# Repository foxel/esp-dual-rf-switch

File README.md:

# LightFox Dual - ESP8266 Dual RF switch for lights

## Connecting the board

The board has following connectors:
* mains connector with sqrew terminals (`Lin`, `L1`, `L2`, `N`). Mains supply should be connected to `Lin` and one of `N` terminals. The loads are connected to `L1`/`L2` and one of `N` terminals.
* ISP connector for ATTiny flashing. Pins are (from left to right): `RST`, `MOSI`, `MISO`, `SCL`)
* switches output connector for debug, etc. These are connected to ATTiny outputs controlling triacs. Pins are (from left to right): `L1`, `L2`, `3V3`, `GND`.

## Schematics

## Layout

## Firmware

There are two microcontrollers to run this switch
* **ESP-01** - use one of available firmware options:
  * ESPurna firmware: https://github.com/foxel/espurna/tree/lightfox-dual
  * Tasmota firmware: https://github.com/foxel/Sonoff-Tasmota/tree/foxel_dual_rf

* **ATTINY441** - firmware is in `attiny-firmware` folder. This requires [ATTinyCore](https://github.com/SpenceKonde/ATTinyCore) to build

To flash ESP module connect it to PC any available way (e.g. USB-Serail adapter + breadboard) and follow selected firmware option flashing instructions.

To flash ATTINY:
* remove ESP-01 module from the header
* connect ISP programmer (i.e. Arduino flashed with ArduinoISP) to ISP port
* use Arduino to flash MC: board is ATTiny441 (installed from [ATTinyCore](https://github.com/SpenceKonde/ATTinyCore))

## BOM

Item | Qty | Reference(s) | Link
-----|-----|--------------|------
100uF, 5v | 1 | C1 | 
3mm red LED | 2 | D1, D2 | 
BTA08-600BW | 2 | D3, D4 | 
1A fuse | 1 | F1 | 
Screw Terminal 01x03 | 2 | J1, J3 | 
4pin header | 2 | J2, J4 | 
470R, 0.125W | 2 | R1, R2 | 
150R, 0.125W | 2 | R3, R4 | 
390R, 0.5W | 2 | R5, R7 | 
470R, 0.5W | 2 | R6, R8 | 
10K, 0.125W | 1 | R9 | 
Itead.cc RF receiver | 1 | RF1 | https://www.itead.cc/rf-receiver-module-433mhz.html
ATTINY441-SSU | 1 | U1 | 
ESP-01S | 1 | U2 | 
MOC3043M/MOC3063M | 2 | U3, U4 | 
HLK-PM03 | 1 | U5 |

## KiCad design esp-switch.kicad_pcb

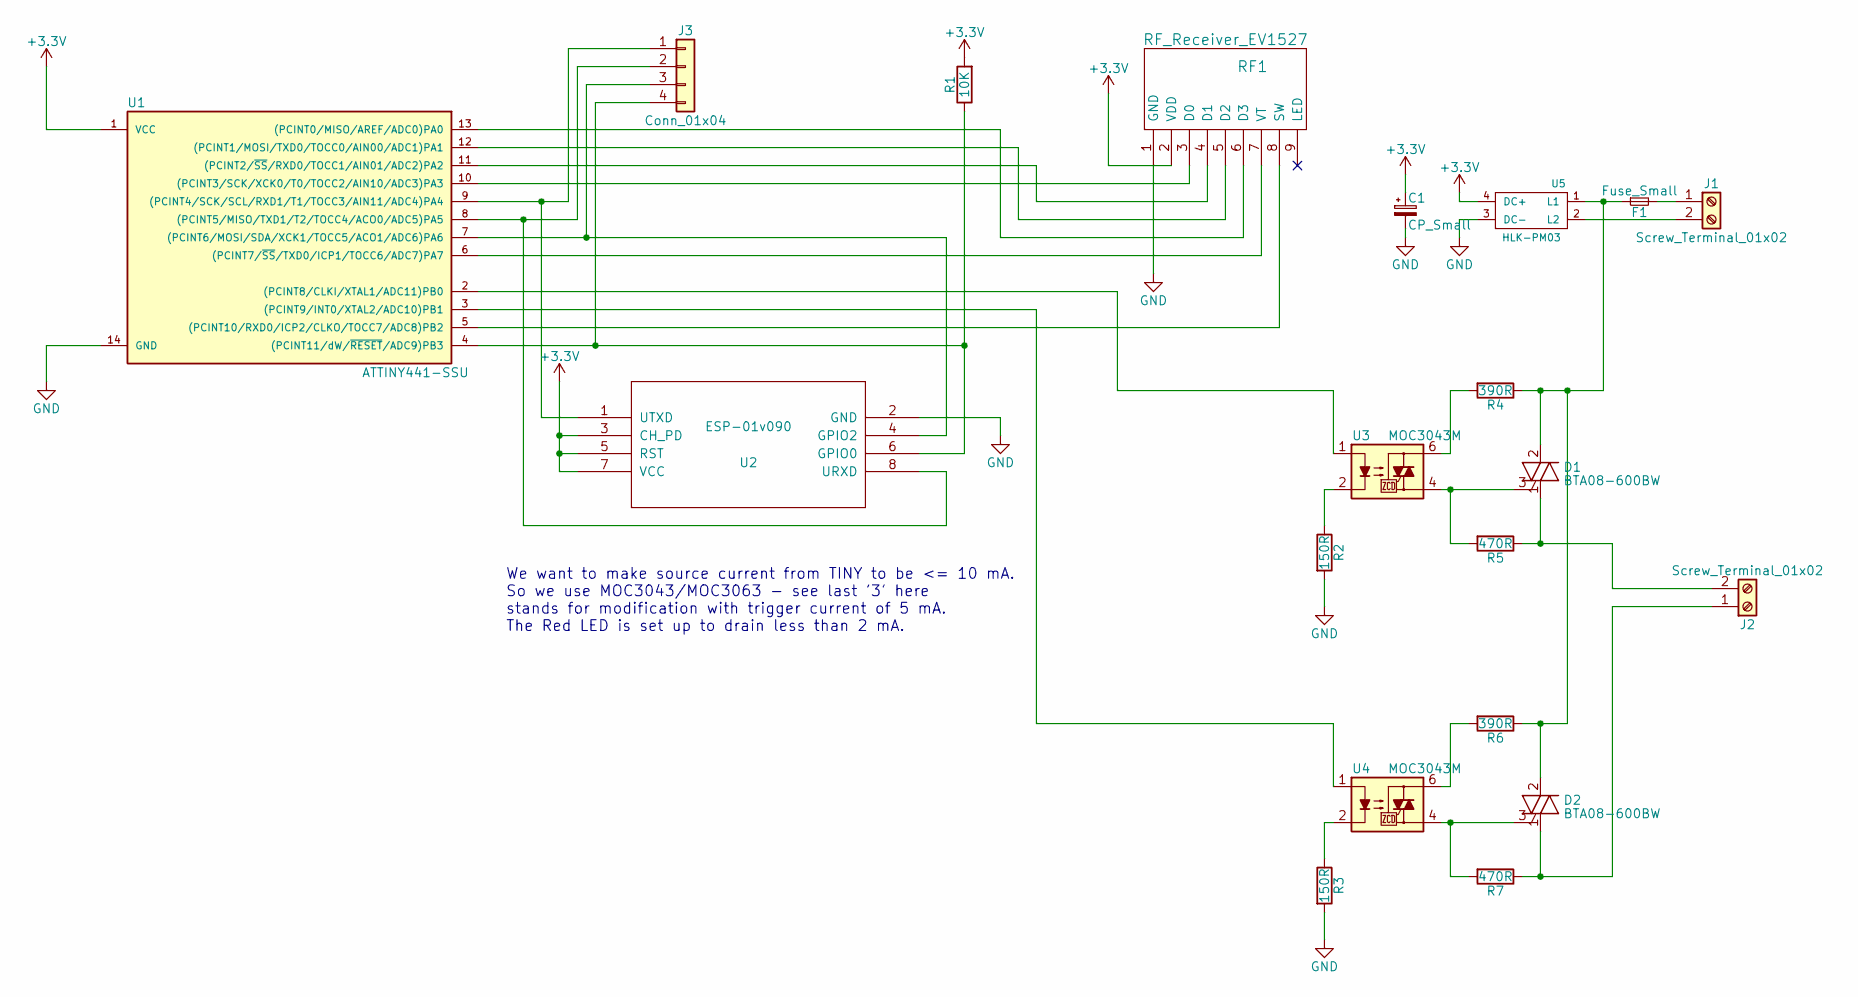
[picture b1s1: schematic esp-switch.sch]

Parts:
C1: CP_Small; CP_Radial_D4.0mm_P2.00mm
D1, D2: BTA08-600BW; TO-220_Vertical
F1: Fuse_Small; R_Axial_DIN0207_L6.3mm_D2.5mm_P7.62mm_Horizontal
J1, J2: Screw_Terminal_01x02; TerminalBlock_Pheonix_MKDS1.5-2pol
J3: Conn_01x04; Pin_Header_Straight_1x04_Pitch2.54mm
R1: 10K; R_Axial_DIN0204_L3.6mm_D1.6mm_P2.54mm_Vertical
R2, R3: 150R; R_Axial_DIN0204_L3.6mm_D1.6mm_P2.54mm_Vertical
R4, R6: 390R; R_Axial_DIN0207_L6.3mm_D2.5mm_P5.08mm_Vertical
R5, R7: 470R; R_Axial_DIN0207_L6.3mm_D2.5mm_P5.08mm_Vertical
RF1: RF_Receiver_EV1527; RF_Receiver_Decoder
U1: ATTINY441-SSU; SOIC-14_3.9x8.7mm_Pitch1.27mm
U2: ESP-01v090; ESP-01
U3, U4: MOC3043M; DIP-6_W7.62mm
U5: HLK-PM03; HLK-PM05

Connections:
+3V3: C1.1, R1.2, RF1.2 (VDD), U1.1 (VCC), U2.3 (CH_PD), U2.5 (RST), U2.7 (VCC), U5.4 (DC+)
GND: C1.2, R2.2, R3.2, RF1.1 (GND), U1.14 (GND), U2.2 (GND), U5.3 (DC-)
unnamed: D1.1 (T1), J2.2, R5.1
unnamed: D1.2 (T2), D2.2 (T2), F1.1, R4.1, R6.1, U5.1 (L1)
unnamed: D1.3 (G), R5.2, U3.4
unnamed: D2.1 (T1), J2.1, R7.1
unnamed: D2.3 (G), R7.2, U4.4
unnamed: F1.2, J1.1
unnamed: J1.2, U5.2 (L2)
unnamed: J3.1, U1.9 ((PCINT4/SCK/SCL/RXD1/T1/TOCC3/AIN11/ADC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), U2.1 (UTXD)
unnamed: J3.2, U1.8 ((PCINT5/MISO/TXD1/T2/TOCC4/ACO0/ADC5)PA5), U2.8 (URXD)
unnamed: J3.3, U1.7 ((PCINT6/MOSI/SDA/XCK1/TOCC5/ACO1/ADC6)P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), U2.4 (GPIO2)
unnamed: J3.4, R1.1, U1.4 ((PCINT11/dW/~RESET~/ADC9)PB3), U2.6 (GPIO0)
unnamed: R2.1, U3.2
unnamed: R3.1, U4.2
unnamed: R4.2, U3.6
unnamed: R6.2, U4.6
unnamed: RF1.3 (D0), U1.10 ((PCINT3/SCK/XCK0/T0/TOCC2/AIN10/ADC3)PA3)
unnamed: RF1.4 (D1), U1.11 ((PCINT2/~SS~/RXD0/TOCC1/AIN01/ADC2)PA2)
unnamed: RF1.5 (D2), U1.12 ((PCINT1/MOSI/TXD0/TOCC0/AIN00/ADC1)PA1)
unnamed: RF1.6 (D3), U1.13 ((PCINT0/MISO/AREF/ADC0)PA0)
unnamed: RF1.7 (VT), U1.6 ((PCINT7/~SS~/TXD0/ICP1/TOCC6/ADC7)PA7)
unnamed: RF1.8 (SW), U1.5 ((PCINT10/RXD0/ICP2/CLKO/TOCC7/ADC8)PB2)
unnamed: U1.2 ((PCINT8/CLKI/XTAL1/ADC11)PB0), U3.1
unnamed: U1.3 ((PCINT9/INT0/XTAL2/ADC10)PB1), U4.1

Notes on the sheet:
We want to make source current from TINY to be <= 10 mA. So we use MOC3043/MOC3063 - see last '3' here stands for modification with trigger current of 5 mA. The Red LED is set up to drain less than 2 mA.

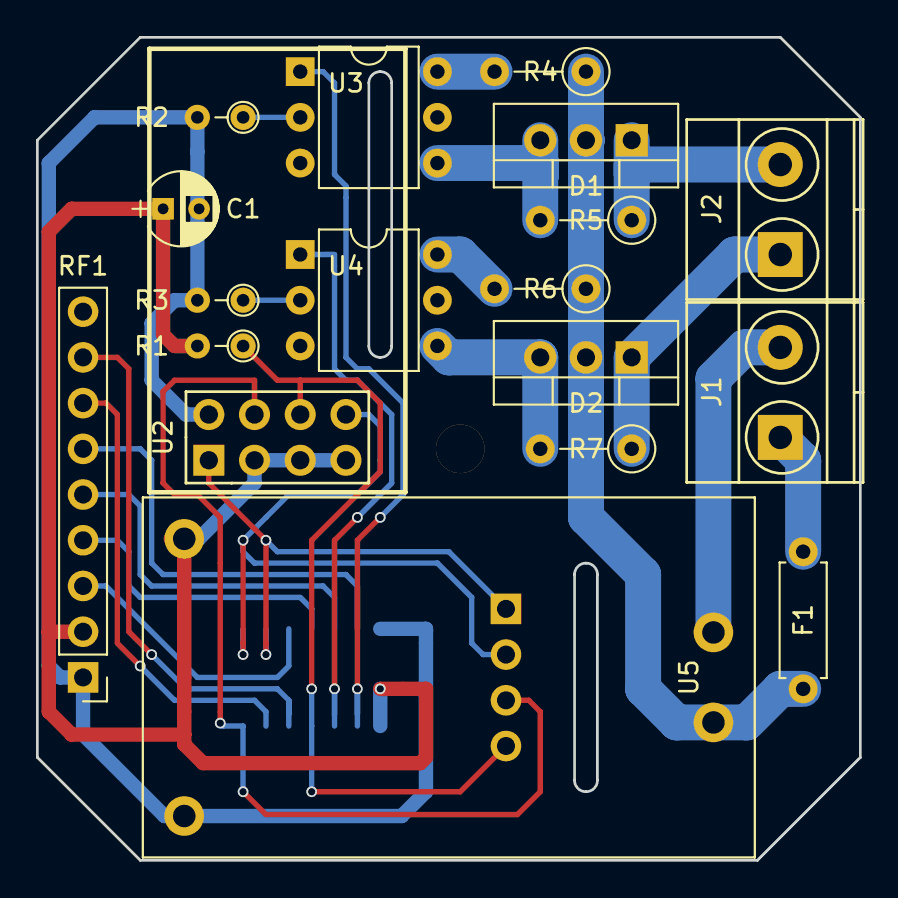
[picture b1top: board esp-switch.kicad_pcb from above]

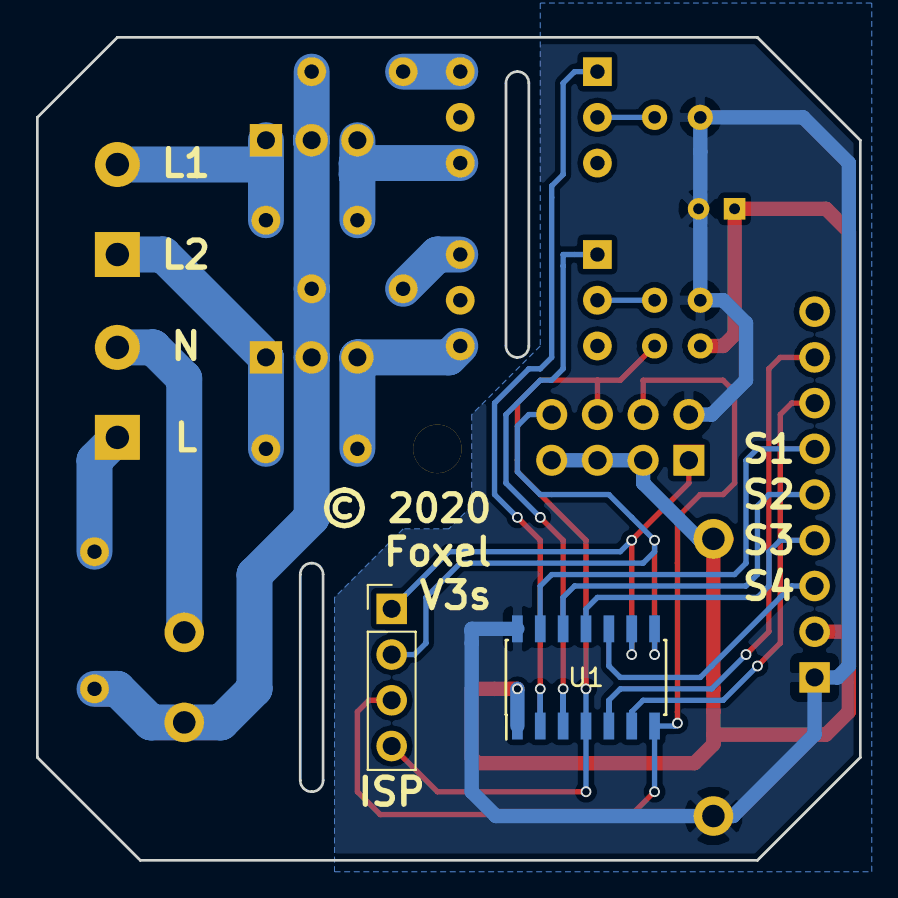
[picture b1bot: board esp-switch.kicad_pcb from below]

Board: 2 copper layers, 45.7 x 45.7 mm, 20 parts (2 on the bottom side), 25 nets.

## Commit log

2018-01-10 initial
2018-01-10 Power supply added
2018-01-10 Single switch source
2018-01-20 Complete layout
2018-01-20 Polishing
2018-01-23 Power circuit fuse
2018-01-23 Capasitor
2018-01-23 Copyright moved
2018-01-27 Some changes
2018-01-27 V2 - traced all the channels from RF
2018-03-09 Added attiny firmware
2018-03-09 Readme
2018-04-02 Added Bind and Clear commands. Changed to send raw buttons from RF to ESP
2018-04-21 Pull-Ups fixed for 441
2018-05-05 V3: mains with shared L and multiple N terminals programming interface for ATTINY moved so can be soldered ATTINY reset available from ESP GPIO0
2018-07-09 Changed components
2018-07-09 Updated readme and pictures
2018-08-01 This project is now given a name: LightFox
2018-08-01 Added more details in README
2019-01-04 Added ESP firmware binaries
2019-01-04 Update README.md
    New firmware flashing instructions
2019-01-05 added gerber files
2020-03-23 V4 schematics
2020-03-23 V4 smaller PCB
2020-06-26 Attiny firmware wallswitch mode (untested)

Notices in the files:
esp-switch.kicad_pcb:
© 2020
